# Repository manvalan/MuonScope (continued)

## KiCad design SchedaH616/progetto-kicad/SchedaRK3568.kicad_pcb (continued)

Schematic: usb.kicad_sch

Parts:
C801: 1uF; C_0603_1608Metric
C802: 100uF/10V; C_1210_3225Metric
C803: 0.1uF; C_0603_1608Metric
J801: TYPE-C-31-M-12; USB-C_SMD-TYPE-C-31-M-12_1; MPN TYPE-C-31-M-12
L801: 90R@100MHz; L_CommonModeChoke_Coilcraft_0805USB; not fitted
R801: 26.1k 1%; R_0603_1608Metric
R802: 100k; R_0603_1608Metric
R804, R805: 22k; R_0603_1608Metric
R806, R807: 2.2R; R_0402_1005Metric
U801: TPS2553DBVR; TPS2553DBVR_SOT-23-6_L2.9-W1.6-P0.95-LS2.8-BR; MPN TPS2553DBVR
U802: USBLC6-2SC6; SOT-23-6; MPN USBLC6-2SC6

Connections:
/5V_SYS: C801.1, R804.1, R805.1, U801.1 (IN); also elsewhere on the board
GND_D: C801.2, C802.2, C803.2, J801.1 (EH), J801.2 (EH), J801.3 (EH), J801.4 (EH), J801.A1B12 (GND), J801.B1A12 (GND), R801.2, R802.2, U801.2 (GND), U802.2 (GND); also elsewhere on the board
USB1_CC1: J801.A5 (CC1), R804.2
USB1_CC2: J801.B5 (CC2), R805.2
USB1_DM: L801.3, R807.1; also elsewhere on the board
USB1_DM_C: J801.A7 (DN1), J801.B7 (DN2), L801.4, R807.2, U802.3 (I/O2), U802.4 (I/O2)
USB1_DP: L801.1, R806.1; also elsewhere on the board
USB1_DP_C: J801.A6 (DP1), J801.B6 (DP2), L801.2, R806.2, U802.1 (I/O1), U802.6 (I/O1)
USB1_ILIM: R801.1, U801.5 (ILIM)
USB1_OC_N: U801.4 (/FAULT); also elsewhere on the board
USB1_VBUS: C802.1, C803.1, J801.A4B9 (VBUS), J801.B4A9 (VBUS), U801.6 (OUT), U802.5 (VBUS)
USB1_VBUS_EN: R802.1, U801.3 (EN); also elsewhere on the board

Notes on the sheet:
USB HOST: USB3_HOST1_DP/DM dell'RK3568 (parte USB 2.0, alimentata da USB3_AVDD) su USB-C (16 pin, HRO TYPE-C-31-M-12), solo host. Serie 8xx. Net USB1_* globali.
La porta non alimenta mai la scheda: VBUS esce solo dal load switch. Rp fissi da 22k a 5V_SYS su CC1/CC2 = sorgente 1.5 A (Type-C), niente controller PD.
TPS2553: EN attivo alto da GPIO0_A6 con 100k a GND, FAULT open-drain su GPIO0_B6 (pull-up 10k a VCC3V3_PMU sul foglio CPU).
RILIM 26.1k 1% = 0.91 / 0.99 / 1.08 A (min/nom/max, tabella 2 del datasheet).
J801 USB-C: DP/DM collegati su entrambi i lati (A6/B6, A7/B7), SBU non connessi, schermo a GND.
Rp 22k a 5 V = 1.5 A (tabella Type-C). Il TPS2553 limita comunque a circa 1 A.
ESD USBLC6-2SC6 vicino al connettore su DP/DM e VBUS. 2.2R in serie (Hardware Design Guide RK3568, USB3_HOST1_DP/DM) in parallelo al choke di modo comune DNP.

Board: 6 copper layers, 443 parts (75 on the bottom side), 314 nets, no tracks yet.

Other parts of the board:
H1, H2, H3, H4: MountingHole_2.2mm_M2

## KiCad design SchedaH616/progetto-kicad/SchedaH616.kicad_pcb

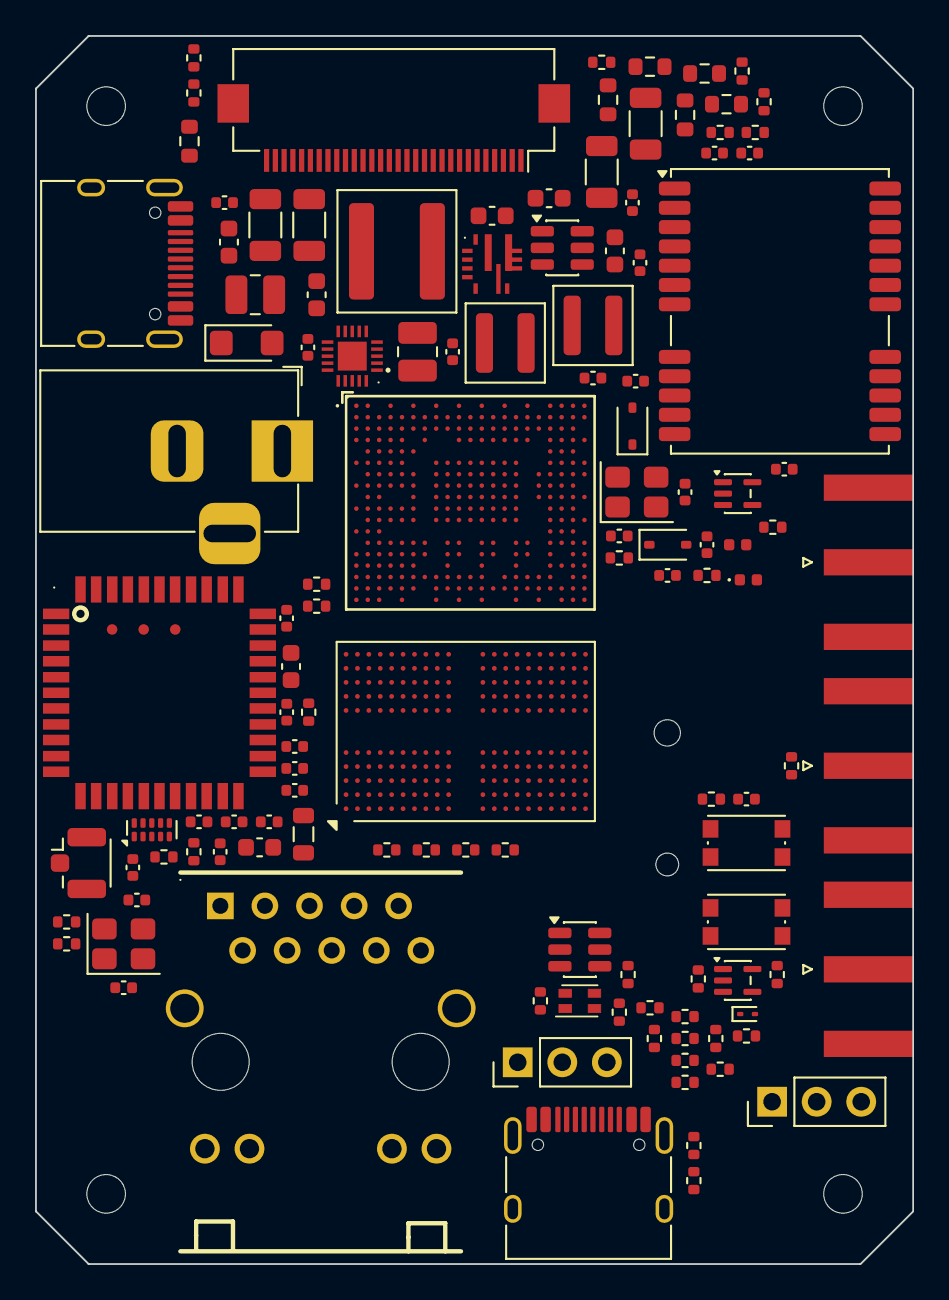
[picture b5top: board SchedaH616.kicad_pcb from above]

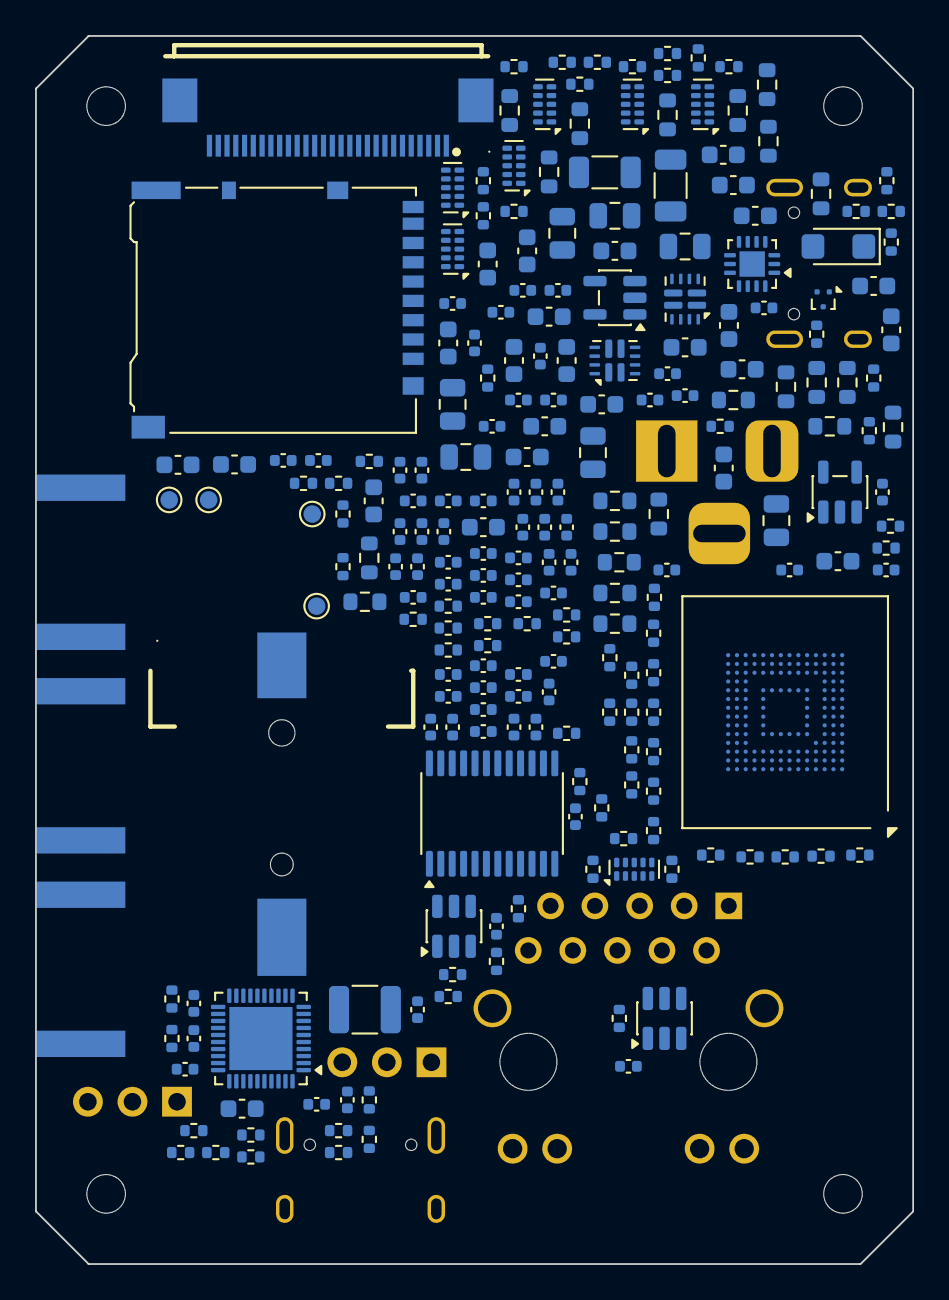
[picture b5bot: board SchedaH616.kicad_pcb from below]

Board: 6 copper layers, 50.0 x 70.0 mm, 356 parts (230 on the bottom side), 289 nets, no tracks yet.

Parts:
BT701: CR1220; BatteryHolder_MYOUNG_BS-12-B3AA003_CR1220
C101, C102: 10uF/25V; C_1206_3216Metric
C103, C109, C110, C132: 100nF; C_0603_1608Metric
C104, C105, C127, C128: 22uF/10V; C_1206_3216Metric
C106, C113, C220, C221: 22uF/10V; C_0805_2012Metric
C107: 4.7uF/10V; C_0603_1608Metric
C108: 1uF; C_0603_1608Metric
C111, C112, C114, C133, C134: 1uF/10V; C_0603_1608Metric
C115, C135: 10uF/10V; C_0805_2012Metric
C125: 100nF/50V; C_0603_1608Metric
C126: 100pF; C_0603_1608Metric
C201, C202, C203: 22uF/10V; C_0603_1608Metric
C204, C205, C206, C216, C218, C219, C226, C227, C228, C230, C501, C514: 100nF; C_0402_1005Metric
C207, C222, C223, C401, C402, C403, C404, C411, C412, C415: 1uF/10V; C_0402_1005Metric
C208, C209, C210, C211, C212, C215, C229: 47uF/6.3V; C_0603_1608Metric
C213, C224, C225, C308, C309, C313, C314, C315, C317, C324, C331, C604, C703, C801: 1uF; C_0402_1005Metric
C214, C231: 4.7uF/10V; C_0402_1005Metric
C217: 10uF/16V; C_0805_2012Metric
C301, C302: 12pF/50V; C_0402_1005Metric
C303: 220nF/16V; C_0402_1005Metric
C304: 1nF/50V; C_0402_1005Metric
C305, C310, C335: 10uF/6.3V; C_0603_1608Metric
C306, C307, C311, C312, C334: 2.2uF/6.3V; C_0402_1005Metric
C316, C318, C319, C320, C321, C322, C323, C325, C326, C327, C328, C332, C333, C405, C406, C407, C408, C409, C410, C413, C414, C417, C418, C420, C421, C423, C505, C506, C507, C508, C510, C511, C512, C513, C515, C602, C605, C702, C705, C706, C803: 0.1uF; C_0402_1005Metric
C329, C330: 470nF/16V; C_0402_1005Metric
C416, C419: 2.2uF/10V; C_0402_1005Metric
C422: 10uF/10V; C_0603_1608Metric
C502, C503: 15pF; C_0402_1005Metric
C504: 22uF; C_0603_1608Metric
C509, C601, C701: 10uF; C_0603_1608Metric
C603: 4.7uF; C_0603_1608Metric
C606, C607: DNP; C_0402_1005Metric
C704: 10nF; C_0402_1005Metric
C802: 100uF/10V; C_1210_3225Metric
D101, D102: SMF5.0A; D_SMF
D701, D704: BAT54; D_SOD-323
D702: ESD5V3U1U-02LS; D_0402_1005Metric
D703: ESD9B5.0ST5G; D_SOD-923
H1, H2, H3, H4: MountingHole_2.2mm_M2
J1: BUS_POWER_MIKILAB; Hirose_FH12-30S-0.5SH_1x30-1MP_P0.50mm_Horizontal
J2: BUS_MIKILAB_MAIN; FPC-05F-28PH20
J103: DC-005-5A-2.0; BarrelJack_Horizontal
J104, J801: TYPE-C-31-M-12; USB_C_Receptacle_HRO_TYPE-C-31-M-12
J301: UART0 debug; PinHeader_1x03_P2.54mm_Vertical
J401: DM3AT-SF-PEJM5; microSD_HC_Hirose_DM3AT-SF-PEJM5
J501: HR911130C; RJ45-TH_HR911130C
J601: U.FL; U.FL_Hirose_U.FL-R-SMT-1_Vertical
J701: SMA antenna; SMA_Amphenol_132289_EdgeMount
J702: SMA PPS OUT; SMA_Amphenol_132289_EdgeMount
J703: SMA STROBE IN; SMA_Amphenol_132289_EdgeMount
J704: PPS/STROBE; PinHeader_1x03_P2.54mm_Vertical
L101: 3.3uH/8A; L_Coilcraft_XAL6030-XXX
L201: 1uH/2.5A; L_1008_2520Metric
L202: 1uH/4A; L_Coilcraft_XAL4020-XXX
L203: 1uH/3A; L_1008_2520Metric
L204: 2.2uH/4A; L_Coilcraft_XAL4020-XXX
L501: 2.2uH; L_0805_2012Metric
L701: 27nH; L_0402_1005Metric
L801: 90R@100MHz; L_CommonModeChoke_Coilcraft_0805USB
R1, R2, R3, R4: 0R; R_0603_1608Metric
R101: 169k 1%; R_0603_1608Metric
R102: 36.1k 1%; R_0603_1608Metric
R103: 73.2k 1%; R_0603_1608Metric
R104, R106, R108, R110, R122, R124, R126: 10k 1%; R_0603_1608Metric
R105, R121: 32.4k 1%; R_0603_1608Metric
R107, R109, R123, R125: 46.4k 1%; R_0603_1608Metric
R111, R127: 22.1k 1%; R_0603_1608Metric
R112: 6.8k 1%; R_0603_1608Metric
R113, R115, R128: 100k; R_0603_1608Metric
R114: 10k; R_0603_1608Metric
R116: 20k; R_0603_1608Metric
R201, R302, R317, R318, R319, R320, R321, R323, R330, R331, R332, R333, R334, R339, R340, R341, R342, R343, R344, R345, R346, R347, R407, R408, R409, R410, R411, R412, R413, R414, R415, R416, R423, R518, R521, R603, R604, R605, R606, R607: 10k; R_0402_1005Metric
R202, R301, R303, R336, R405, R520, R608, R806, R807: 0R; R_0402_1005Metric
R203, R322, R601, R602, R706, R802: 100k; R_0402_1005Metric
R204: 33.2k 1%; R_0402_1005Metric
R205: 10k 1%; R_0402_1005Metric
R304, R403, R404: 240R 1%; R_0402_1005Metric
R305, R306, R307, R308, R309, R310, R406, R417, R703, R704: 33R; R_0402_1005Metric
R311, R312, R313, R314, R315, R316, R338, R705: 100R; R_0402_1005Metric
R324, R325, R507, R508, R509, R510, R511, R512, R513, R514, R515, R517: 4.7k; R_0402_1005Metric
R326, R327, R328, R329: 2.2k; R_0402_1005Metric
R337: 150k 1%; R_0402_1005Metric
R401, R402: 100k 1%; R_0402_1005Metric
R418, R419, R420, R421, R422: 47k; R_0402_1005Metric
R501, R502, R503, R504, R505, R506: 22R; R_0402_1005Metric
R516: 1.5k; R_0402_1005Metric
R519: 2.49k 1%; R_0402_1005Metric
R522, R523: 510R; R_0402_1005Metric
R702: 10R; R_0402_1005Metric
R801: 26.1k 1%; R_0402_1005Metric
R804, R805: 22k; R_0402_1005Metric
SW301: RESET; SW_Push_1P1T_NO_CK_KMR2
SW302: FEL; SW_Push_1P1T_NO_CK_KMR2
TP101: MUX2_ST; TestPoint_Pad_D1.0mm
TP201: PWRON; TestPoint_Pad_D1.0mm
TP701: SAFEBOOT_N; TestPoint_Pad_D1.0mm
TP702: RESET_N; TestPoint_Pad_D1.0mm
U101: TPS56637RPAR; Texas_RPA0010A_VQFN-HR-10_3x3mm
U103, U108: TPS2121RUXR; Texas_VQFN-HR-12_2x2.5mm_P0.5mm
U104: FUSB302BMPX; WQFN-14-1EP_2.5x2.5mm_P0.5mm_EP1.45x1.45mm
U105: SY6280AAC; SOT-23-5
U107: TPD2EUSB30ADRTR; Texas_DRT-3
U201: AXP313A; QFN-20_L3.0-W3.0-P0.40-BL-EP1.7
U202: TPS563201DDCR; SOT-23-6
U203: AP2112K-1.8TRG1; SOT-23-5
U301: H616; BGA-284_L14.0-W12.0-P0.65-TL
U302, U303, U304, U305, U306, U307, U403, U404: TPD4E05U06DQA; USON-10_2.5x1.0mm_P0.5mm
U308: TCA6416APWR; TSSOP-24_4.4x7.8mm_P0.65mm
U401: MT53E512M32D1ZW-046 IT:B; BGA-200_10x14.5mm_Layout12x22_P0.8x0.65mm
U402: FEMDNN064G-C9A61; LFBGA-153_11.5x13mm_Layout14x14_P0.5mm
U501: RTL8211F-CG; QFN-40-1EP_5x5mm_P0.4mm_EP3.6x3.6mm
U502: 25AA02E48T-I/OT; SOT-23-6
U601: AP6256; AP6256_LGA-47_12x12mm
U701: NEO-M9N-00B; ublox_NEO
U702, U703: 74LVC1G17; SOT-353_SC-70-5
U801: TPS2553DBVR; SOT-23-6
U802: USBLC6-2SC6; SOT-23-6
Y301: 24MHz; Crystal_SMD_3225-4Pin_3.2x2.5mm
Y501: 25MHz; Crystal_SMD_3225-4Pin_3.2x2.5mm

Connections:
/3V3_PERI: C220.1, C221.1, C222.1, C416.1, C417.1, C418.1, C422.1, C423.1, C509.1, C510.1, C511.1, C512.1, C513.1, C515.1, C601.1, C602.1, C701.1, C702.1, C705.1, C706.1, D701.2, J401.4, L204.2, R204.1, R418.1, R419.1, R420.1, R421.1, R422.1, R507.1, R511.1, R512.1, R513.1, R516.1, R517.1, R518.1, R521.1, U203.1, U203.3, U402.E6, U402.F5, U402.J10, U402.K9, U501.11, U501.28, U501.29, U501.40, U502.6, U601.9, U601.23, U701.23, U702.5, U703.5
/3V3_SYS: C108.1, C109.1, R336.2, U104.3, U104.4
/5V_SYS: C113.1, C114.1, C201.1, C202.1, C203.1, C204.1, C205.1, C206.1, C217.1, C218.1, C801.1, R203.1, R804.1, R805.1, U103.1, U103.8, U201.2, U201.17, U201.20, U202.3, U801.1
/AP-RESET: R201.2, R338.1, U201.13
/Alimentazione/5V_BUCK: C104.1, C105.1, C127.1, C128.1, C133.1, L101.2, R103.1, R115.1, R116.1, R121.1, R123.1, U108.7
/Alimentazione/5V_EXT: C111.1, C115.1, C135.1, R105.1, R107.1, R128.1, U103.7, U105.5, U108.1, U108.8
/Alimentazione/5V_JACK: C106.1, C134.1, D101.1, J103.1, R125.1, U108.2
/Alimentazione/BUCK_BST: C103.1, U101.7
/Alimentazione/BUCK_EN: R101.2, R102.1, U101.1
/Alimentazione/BUCK_FB: C126.2, R103.2, R104.1, U101.2
/Alimentazione/BUCK_FF: C126.1, R116.2
/Alimentazione/BUCK_MODE: R114.1, U101.10
/Alimentazione/BUCK_PG: R115.2, U101.4
/Alimentazione/BUCK_SW: C103.2, L101.1, U101.6
/Alimentazione/MUX2_ILM: R127.1, U108.10
/Alimentazione/MUX2_OV1: R123.2, R124.1, U108.5
/Alimentazione/MUX2_OV2: R125.2, R126.1, U108.4
/Alimentazione/MUX2_PR1: R121.2, R122.1, U108.6
/Alimentazione/MUX2_SS: C132.1, U108.11
/Alimentazione/MUX2_ST: R128.2, TP101.1, U108.9
/Alimentazione/MUX_ILM: R111.1, U103.10
/Alimentazione/MUX_OV1: R107.2, R108.1, U103.5
/Alimentazione/MUX_OV2: R109.2, R110.1, U103.4
/Alimentazione/MUX_PR1: R105.2, R106.1, U103.6
/Alimentazione/MUX_SS: C110.1, U103.11
/Alimentazione/SRC_ISET: R112.1, U105.3
/Alimentazione/USBC_CC1: J104.A5, U104.10, U104.11, U107.1
/Alimentazione/USBC_CC2: J104.B5, U104.1, U104.14, U107.2
/Alimentazione/VBUS: C107.1, C112.1, D102.1, J104.A4, J104.A9, J104.B4, J104.B9, R109.1, U103.2, U104.2, U105.1
/Bus MIKILAB/BUS_1V25_REF: J1.6, J2.6
/Bus MIKILAB/BUS_2V5_REF: J1.5, J2.5
/Bus MIKILAB/BUS_3V3: J1.9, J1.29, J2.3
/Bus MIKILAB/BUS_5V: J1.8, J2.2
/Bus MIKILAB/BUS_VBIAS_1: J1.2, J2.8
/Bus MIKILAB/BUS_VBIAS_2: J1.3, J2.9
/Bus MIKILAB/SPI_ID_0: J2.25, R1.1
/Bus MIKILAB/SPI_ID_1: J2.26, R2.1
/Bus MIKILAB/SPI_ID_2: J2.27, R3.1
/CPU/DCXO_XIN: C301.1, U301.B11, Y301.1
/CPU/DCXO_XOUT: R301.1, U301.C12
/CPU/DCXO_XOUT_R: C302.1, R301.2, Y301.3
/CPU/IOX_INT_N: R330.2, U301.C1, U308.1
/CPU/IOX_RESET_N: R331.2, U308.3
/CPU/SOC_AC_VRA1: C331.1, U301.C17
/CPU/SOC_ADDR_0: R311.1, U301.C3
/CPU/SOC_ADDR_1: R312.1, U301.A2
/CPU/SOC_ADDR_2: R313.1, U301.B2
/CPU/SOC_AGND: C329.2, C330.2, R303.1, R337.2, U301.H18
/CPU/SOC_BOOT_SEL1: R340.2, R341.1, U301.D1
/CPU/SOC_BOOT_SEL2: R342.2, R343.1, U301.D2
/CPU/SOC_DXLDO: C303.1, U301.D13
/CPU/SOC_FEL: R302.2, SW302.1, U301.B17
/CPU/SOC_PREFIX_0: R314.1, U301.H5
/CPU/SOC_PREFIX_1: R315.1, U301.K6
/CPU/SOC_PREFIX_2: R316.1, U301.K2
/CPU/SOC_RESET: C304.1, R338.2, R339.2, SW301.1, U301.A16
/CPU/SOC_REXT: R337.1, U301.K18
/CPU/SOC_SZQ: R304.1, U301.L15
/CPU/SOC_VRA1: C329.1, U301.J18
/CPU/SOC_VRA2: C330.1, U301.J17
/CPU/UART0_RX: J301.2, U301.D15
/CPU/UART0_TX: J301.1, U301.D16
/DAC61402_FAULT: J1.20, R323.2, U304.1, U308.6
/MAIN_HIT_N: J2.28, R325.2, U301.C9, U307.4
/MAIN_I2C_SCL: J2.15, R326.2, U301.B15, U305.2
/MAIN_I2C_SDA: J2.14, R327.2, U301.C15, U305.1
/MAIN_SPI_ADDR_0: J2.18, R311.2, U305.5
/MAIN_SPI_ADDR_1: J2.19, R312.2, U306.1
/MAIN_SPI_ADDR_2: J2.20, R313.2, U306.2
/MAIN_SPI_ALERT_N: J2.24, R324.2, U301.B10, U307.2
/MAIN_SPI_CS_MASTER: J2.17, R320.2, U301.B14, U305.4
/MAIN_SPI_MISO: J2.13, R310.2, U304.5
/MAIN_SPI_MOSI: J2.12, R309.2, U304.4
/MAIN_SPI_PREFIX_0: J2.21, R314.2, U306.4
/MAIN_SPI_PREFIX_1: J2.22, R315.2, U306.5
/MAIN_SPI_PREFIX_2: J2.23, R316.2, U307.1
/MAIN_SPI_SCLK: J2.11, R308.2, U304.2
/Memorie/LP_ODT_A: R401.2, U401.G2
/Memorie/LP_ODT_B: R402.2, U401.T2
/Memorie/LP_ZQ0: R403.2, U401.A5
/Memorie/LP_ZQ1: R404.2, U401.A8
/PD_INT_N: R332.2, U104.5, U301.F4
/PMIC/PERI_BST: C219.1, U202.6
/PMIC/PERI_EN: R202.2, R203.2, U202.5
/PMIC/PERI_FB: R204.2, R205.1, U202.4
/PMIC/PERI_SW: C219.2, L204.1, U202.2
/PMIC/PMU_LX1: L201.1, U201.18
/PMIC/PMU_LX2: L202.1, U201.19
/PMIC/PMU_LX3: L203.1, U201.3
/PMIC/PMU_PWRON: C216.1, TP201.1, U201.14
/PMIC/PMU_RTCLDO: C231.1, U201.7
/PMIC/PMU_VREF: C207.1, U201.8
/PMU-SCK: R328.2, U104.6, U201.6, U301.C18, U308.22
/PMU-SDA: R329.2, U104.7, U201.5, U301.B18, U308.23
/PWR_SPI_DAC_CS: J1.17, R319.2, U301.B13, U303.2
/PWR_SPI_INA239A_CS: J1.15, R317.2, U301.A12, U302.5
/PWR_SPI_INA239B_CS: J1.16, R318.2, U301.A14, U303.1
/PWR_SPI_MISO: J1.13, R307.2, U302.4
/PWR_SPI_MOSI: J1.12, R306.2, U302.2
/PWR_SPI_SCLK: J1.11, R305.2, U302.1
/PWR_SRC_ST: R334.2, U103.9, U308.9
/Rete/ETH_CT: C514.1, J501.P1
/Rete/ETH_LED1_A: J501.11, R522.2
/Rete/ETH_LED2_A: J501.14, R523.2
/Rete/MDI0_N: J501.P3, U501.2
/Rete/MDI0_P: J501.P2, U501.1
/Rete/MDI1_N: J501.P7, U501.5
/Rete/MDI1_P: J501.P4, U501.4
/Rete/MDI2_N: J501.P6, U501.7
/Rete/MDI2_P: J501.P5, U501.6
/Rete/MDI3_N: J501.P9, U501.10
/Rete/MDI3_P: J501.P8, U501.9
/USB0_DM: J104.A7, J104.B7, U301.J19
/USB0_DP: J104.A6, J104.B6, U301.J20
/VBIAS_ENABLE: J1.19, R322.1, U303.5, U308.5
/VBUS_SRC_EN: R113.1, U105.4, U308.8
/VCC-1V8: C214.1, C317.1, C318.1, C319.1, C320.1, C321.1, C322.1, C332.1, C334.1, C335.1, C411.1, C412.1, C413.1, C414.1, R201.1, R328.1, R329.1, R331.1, R339.1, U201.15, U301.D11, U301.D12, U301.D18, U301.F18, U301.H17, U301.H20, U301.L14, U308.2, U401.F1, U401.F12, U401.G4, U401.G9, U401.T4, U401.T9, U401.U1, U401.U12
/VCC-1V8-EMMC: C223.1, C323.1, C419.1, C420.1, C421.1, R330.1, R332.1, R333.1, R340.1, R342.1, R344.1, R346.1, R407.1, R408.1, R409.1, R410.1, R411.1, R412.1, R413.1, R414.1, R415.1, R416.1, U203.5, U301.F5, U402.C6, U402.M4, U402.N4, U402.P3, U402.P5
/VCC-DRAM: C212.1, C213.1, C229.1, C230.1, C314.1, C315.1, C316.1, C401.1, C402.1, C403.1, C404.1, C405.1, C406.1, C407.1, C408.1, C409.1, C410.1, L203.2, R401.1, R402.1, R403.1, R404.1, R405.1, U301.L9, U301.L10, U301.L11, U301.L12, U301.L13, U401.A4, U401.A9, U401.AA3, U401.AA5, U401.AA8, U401.AA10, U401.AB4, U401.AB9, U401.B3, U401.B5, U401.B8, U401.B10, U401.D1, U401.D5, U401.D8, U401.D12, U401.F3, U401.F5, U401.F8, U401.F10, U401.H1, U401.H5, U401.H8, U401.H12, U401.K1, U401.K3, U401.K10, U401.K12, U401.N1, U401.N3, U401.N10, U401.N12, U401.R1, U401.R5, U401.R8, U401.R12, U401.U3, U401.U5, U401.U8, U401.U10, U401.W1, U401.W5, U401.W8, U401.W12
/VCC-DRAM-FB: R405.2, U201.4
/VCC-IO: C215.1, C226.1, C324.1, C325.1, C326.1, C327.1, C328.1, C333.1, C604.1, C605.1, R202.1, R302.1, R317.1, R318.1, R319.1, R320.1, R323.1, R324.1, R325.1, R326.1, R327.1, R334.1, R336.1, R423.1, R603.1, R604.1, R605.1, R606.1, R607.1, U201.12, U301.D7, U301.D10, U301.E18, U301.J6, U301.M18, U308.24, U601.22
/VDD-CPU: C210.1, C211.1, C225.1, C228.1, C305.1, C306.1, C307.1, C308.1, C309.1, L202.2, U301.H8, U301.H9, U301.J8, U301.J9, U301.J10, U301.J11
/VDD-CPUFB: U201.1, U301.L8
/VDD-SYS: C208.1, C209.1, C224.1, C227.1, C310.1, C311.1, C312.1, C313.1, L201.2, U301.F9, U301.F10, U301.F11, U301.F12, U301.F13, U301.G8, U301.G9, U301.G10, U301.G11, U301.G12
/VDD-SYSFB: U201.16, U301.F8
/VIN_SYS: C101.1, C102.1, C125.1, J1.24, J1.25, J1.26, R101.1, U101.8
/VREF_ENABLE: J1.18, R321.1, U303.4, U308.4
BT_HOST_WAKE: U308.16, U601.7
BT_REG_ON: R602.1, U308.14, U601.34
BT_UART_CTS: U301.B3, U601.41
BT_UART_RTS: U301.C4, U601.44
BT_UART_RX: U301.B4, U601.42
BT_UART_TX: U301.A4, U601.43
BT_WAKE: U308.15, U601.6
DRAM_A0: U301.T21, U401.H9, U401.R9
DRAM_A1: U301.U17, U401.H2, U401.R2
DRAM_A2: U301.T18, U401.H4, U401.R4
DRAM_A3: U301.T16, U401.J11, U401.P11
DRAM_A4: U301.R18, U401.H11, U401.R11
DRAM_A5: U301.P15, U401.H3, U401.R3
DRAM_CKE0: U301.V15, U401.J4, U401.P4
DRAM_CKE1: U301.P13, U401.J5, U401.P5
DRAM_CKN: U301.U14, U401.J9, U401.P9
DRAM_CKP: U301.T14, U401.J8, U401.P8
DRAM_CS0: U301.V17, U401.J2, U401.P2
DRAM_CS1: U301.R20, U401.H10, U401.R10
DRAM_DQ0: U301.N3, U401.B2
DRAM_DQ1: U301.U4, U401.C2
DRAM_DQ2: U301.N2, U401.E2
DRAM_DQ3: U301.T4, U401.F2
DRAM_DQ4: U301.U3, U401.F4
DRAM_DQ5: U301.P1, U401.E4
DRAM_DQ6: U301.T2, U401.C4
DRAM_DQ7: U301.P2, U401.B4
DRAM_DQ8: U301.P5, U401.B11
DRAM_DQ9: U301.V3, U401.C11
DRAM_DQ10: U301.P4, U401.E11
DRAM_DQ11: U301.R4, U401.F11
DRAM_DQ12: U301.R6, U401.F9
DRAM_DQ13: U301.N4, U401.E9
DRAM_DQ14: U301.P6, U401.C9
DRAM_DQ15: U301.N5, U401.B9
DRAM_DQ16: U301.T11, U401.AA2
DRAM_DQ17: U301.U12, U401.Y2
DRAM_DQ18: U301.T12, U401.V2
DRAM_DQ19: U301.U9, U401.U2
DRAM_DQ20: U301.T6, U401.U4
DRAM_DQ21: U301.U5, U401.V4
DRAM_DQ22: U301.T7, U401.Y4
DRAM_DQ23: U301.T5, U401.AA4
DRAM_DQ24: U301.R9, U401.AA11
DRAM_DQ25: U301.P7, U401.Y11
DRAM_DQ26: U301.N7, U401.V11
DRAM_DQ27: U301.P9, U401.U11
DRAM_DQ28: U301.P10, U401.U9
DRAM_DQ29: U301.U11, U401.V9
DRAM_DQ30: U301.P12, U401.Y9
DRAM_DQ31: U301.R12, U401.AA9
DRAM_DQM0: U301.U1, U401.C3
DRAM_DQM1: U301.R3, U401.C10
DRAM_DQM2: U301.T9, U401.Y3
DRAM_DQM3: U301.N10, U401.Y10
DRAM_DQS0N: U301.R1, U401.E3
DRAM_DQS0P: U301.R2, U401.D3
DRAM_DQS1N: U301.V2, U401.E10
DRAM_DQS1P: U301.U2, U401.D10
DRAM_DQS2N: U301.U8, U401.V3
DRAM_DQS2P: U301.V8, U401.W3
DRAM_DQS3N: U301.U10, U401.V10
DRAM_DQS3P: U301.V10, U401.W10
DRAM_RST: U301.U21, U401.T11
EMMC_CLK: R344.2, R345.1, R406.1, U301.D3
EMMC_CLK_M: R406.2, U402.M6
EMMC_CMD: R346.2, R347.1, R407.2, U301.E2, U402.M5
EMMC_D0: R408.2, U301.F2, U402.A3
EMMC_D1: R409.2, U301.G3, U402.A4
EMMC_D2: R410.2, U301.H2, U402.A5
EMMC_D3: R411.2, U301.E3, U402.B2
EMMC_D4: R412.2, U301.F1, U402.B3
EMMC_D5: R413.2, U301.F3, U402.B4
EMMC_D6: R414.2, U301.H1, U402.B5
EMMC_D7: R415.2, U301.H3, U402.B6
EMMC_DS: U301.B1, U402.H5
EMMC_RST: R416.2, U301.C2, U402.K5
EMMC_VDDI: C415.1, U402.C2
GND_A: J1.1, J1.4, J1.7, J2.7, R4.1
GND_D: BT701.2, C101.2, C102.2, C104.2, C105.2, C106.2, C107.2, C108.2, C109.2, C110.2, C111.2, C112.2, C113.2, C114.2, C115.2, C125.2, C127.2, C128.2, C132.2, C133.2, C134.2, C135.2, C201.2, C202.2, C203.2, C204.2, C205.2, C206.2, C207.2, C208.2, C209.2, C210.2, C211.2, C212.2, C213.2, C214.2, C215.2, C216.2, C217.2, C218.2, C220.2, C221.2, C222.2, C223.2, C224.2, C225.2, C226.2, C227.2, C228.2, C229.2, C230.2, C231.2, C301.2, C302.2, C303.2, C304.2, C305.2, C306.2, C307.2, C308.2, C309.2, C310.2, C311.2, C312.2, C313.2, C314.2, C315.2, C316.2, C317.2, C318.2, C319.2, C320.2, C321.2, C322.2, C323.2, C324.2, C325.2, C326.2, C327.2, C328.2, C331.2, C332.2, C333.2, C334.2, C335.2, C401.2, C402.2, C403.2, C404.2, C405.2, C406.2, C407.2, C408.2, C409.2, C410.2, C411.2, C412.2, C413.2, C414.2, C415.2, C416.2, C417.2, C418.2, C419.2, C420.2, C421.2, C422.2, C423.2, C501.2, C502.2, C503.2, C504.2, C505.2, C506.2, C507.2, C508.2, C509.2, C510.2, C511.2, C512.2, C513.2, C514.2, C515.2, C601.2, C602.2, C603.2, C604.2, C605.2, C606.2, C607.2, C701.2, C702.2, C703.2, C704.2, C705.2, C706.2, C801.2, C802.2, C803.2, D101.2, D102.2, D702.2, D703.2, J1.10, J1.14, J1.21, J1.22, J1.23, J1.27, J1.28, J1.30, J1.MP, J2.1, J2.4, J2.10, J2.16, J2.MP, J103.2, J103.3, J104.A1, J104.A12, J104.B1, J104.B12, J104.SH, J301.3, J401.6, J401.10, J401.SH, J501.12, J501.13, J501.P10, J501.SHIELD0, J501.SHIELD1, J601.2, J701.2, J702.2, J703.2, J704.3, J801.A1, J801.A12, J801.B1, J801.B12, J801.SH, R1.2, R2.2, R3.2, R4.2, R102.2, R104.2, R106.2, R108.2, R110.2, R111.2, R112.2, R113.2, R114.2, R122.2, R124.2, R126.2, R127.2, R205.2, R303.2, R304.2, R321.2, R322.2, R341.2, R343.2, R345.2, R347.2, R508.2, R509.2, R510.2, R514.2, R515.2, R519.2, R601.2, R602.2, R706.2, R801.2, R802.2, SW301.2, SW302.2, U101.3, U101.9, U103.3, U103.12, U104.8, U104.9, U104.15, U105.2, U107.3, U108.3, U108.12, U201.9, U201.21, U202.1, U203.2, U301.A1, U301.A10, U301.A18, U301.A21, U301.B6, U301.B16, U301.D19, U301.F14, U301.F15, U301.G13, U301.G14, U301.G15, U301.H10, U301.H11, U301.H12, U301.H13, U301.H14, U301.H15, U301.H19, U301.J12, U301.J13, U301.J14, U301.J15, U301.K8, U301.K9, U301.K10, U301.K11, U301.K12, U301.K13, U301.K14, U301.K15, U301.L21, U301.M1, U301.M2, U301.M3, U301.N6, U301.N9, U301.N12, U301.N15, U301.N18, U301.P3, U301.R5, U301.R21, U301.T1, U301.T3, U301.T8, U301.T10, U301.T15, U301.T17, U301.U6, U301.U13, U301.V1, U301.V5, U301.V12, U301.V19, U301.V21, U302.3, U302.8, U303.3, U303.8, U304.3, U304.8, U305.3, U305.8, U306.3, U306.8, U307.3, U307.8, U308.12, U308.21, U401.A3, U401.A10, U401.AB3, U401.AB5, U401.AB8, U401.AB10, U401.C1, U401.C5, U401.C8, U401.C12, U401.D2, U401.D4, U401.D9, U401.D11, U401.E1, U401.E5, U401.E8, U401.E12, U401.G1, U401.G3, U401.G5, U401.G8, U401.G10, U401.G12, U401.J1, U401.J3, U401.J10, U401.J12, U401.K2, U401.K4, U401.K9, U401.K11, U401.N2, U401.N4, U401.N9, U401.N11, U401.P1, U401.P3, U401.P10, U401.P12, U401.T1, U401.T3, U401.T5, U401.T8, U401.T10, U401.T12, U401.V1, U401.V5, U401.V8, U401.V12, U401.W2, U401.W4, U401.W9, U401.W11, U401.Y1, U401.Y5, U401.Y8, U401.Y12, U402.A6, U402.C4, U402.E7, U402.G5, U402.H10, U402.J5, U402.K8, U402.N2, U402.N5, U402.P4, U402.P6, U403.3, U403.8, U404.3, U404.8, U501.41, U502.2, U601.1, U601.3, U601.20, U601.29, U601.31, U601.33, U601.36, U701.7, U701.10, U701.12, U701.13, U701.24, U702.3, U703.3, U801.2, U802.2, Y301.2, Y301.4, Y501.2, Y501.4
GNSS_ANT_BIAS: C704.1, L701.1, R702.2
GNSS_BAT: BT701.1, D704.2
GNSS_EXTINT: U301.B9, U701.4, U703.4
GNSS_PPS: R703.2, U301.C10
GNSS_PPS_BUF: R704.1, U702.4
GNSS_PPS_OUT: J702.1, J704.1, R704.2
GNSS_RESET_N: TP702.1, U701.8
GNSS_RF_IN: D702.1, J701.1, L701.2, U701.11
GNSS_SAFEBOOT_N: TP701.1, U701.1
GNSS_STROBE_IN: D703.1, J703.1, J704.2, R705.1
GNSS_STROBE_R: R705.2, R706.1, U703.2
GNSS_TP: R703.1, U701.3, U702.2
GNSS_UART2_RX: U301.B8, U701.20
GNSS_UART2_TX: U301.A8, U701.21
GNSS_VCC_RF: R702.1, U701.9
GNSS_V_BCKP: C703.1, D701.1, D704.1, U701.22
PHY_CLKOUT: R520.1, U501.35
PHY_EE_CS_N: R521.2, U308.19, U502.5
PHY_INT_N: R517.2, U308.11, U501.31
PHY_LED0: R513.2, U501.32
PHY_LED1: R514.1, R522.1, U501.33
PHY_LED2: R515.1, R523.1, U501.34
PHY_MDC: U301.L6, U501.13
PHY_MDIO: R516.2, U301.L4, U501.14
PHY_REG_OUT: L501.1, U501.30
PHY_RSET: R519.1, U501.39
PHY_RST_N: C501.1, R518.2, U308.10, U501.12
PHY_TXCTL_P: R506.2, U501.19
PHY_TXC_P: R501.2, U501.20
PHY_TXD0_P: R502.2, U501.18
PHY_TXD1_P: R503.2, U501.17
PHY_TXD2_P: R504.2, U501.16
PHY_TXD3_P: R505.2, U501.15
PHY_VDD10: C504.1, C505.1, C506.1, C507.1, C508.1, L501.2, U501.3, U501.8, U501.21, U501.38
PHY_XI: C502.1, U501.36, Y501.1
PHY_XO: C503.1, U501.37, Y501.3
RGMII_CLKIN: R520.2, U301.E5
RGMII_RXCK: R508.1, U301.G5, U501.27
RGMII_RXCTL: R509.1, U301.H4, U501.26
RGMII_RXD0: R512.2, U301.E4, U501.25
RGMII_RXD1: R511.2, U301.G6, U501.24
RGMII_RXD2: R510.1, U301.D4, U501.23
RGMII_RXD3: R507.2, U301.H6, U501.22
RGMII_TXCK: R501.1, U301.K4
RGMII_TXCTL: R506.1, U301.K5
RGMII_TXD0: R502.1, U301.L5
RGMII_TXD1: R503.1, U301.D5
RGMII_TXD2: R504.1, U301.E6
RGMII_TXD3: R505.1, U301.G4
SD_CLK: R417.1, U301.K1
SD_CLK_S: J401.5, R417.2, U403.1
SD_CMD: J401.3, R418.2, U301.K3, U403.2
SD_D0: J401.7, R419.2, U301.J3, U403.4
SD_D1: J401.8, R420.2, U301.J2, U403.5
SD_D2: J401.1, R421.2, U301.L3, U404.1
SD_D3: J401.2, R422.2, U301.L2, U404.2
SD_DET: J401.9, R423.2, U308.18, U404.4
SPI1_CLK: R305.1, R308.1, U301.C14, U502.1
SPI1_MISO: R307.1, R310.1, U301.C13, U502.4
SPI1_MOSI: R306.1, R309.1, U301.B12, U502.3
USB1_CC1: J801.A5, R804.2
USB1_CC2: J801.B5, R805.2
USB1_DM: L801.3, R807.1, U301.M19
USB1_DM_C: J801.A7, J801.B7, L801.4, R807.2, U802.3, U802.4
USB1_DP: L801.1, R806.1, U301.M20
USB1_DP_C: J801.A6, J801.B6, L801.2, R806.2, U802.1, U802.6
USB1_ILIM: R801.1, U801.5
USB1_OC_N: R333.2, U301.G2, U801.4
USB1_VBUS: C802.1, C803.1, J801.A4, J801.A9, J801.B4, J801.B9, U801.6, U802.5
USB1_VBUS_EN: R802.1, U308.7, U801.3
WIFI_32K: U301.C8, U601.24
WL_ANT: C606.1, R608.1, U601.2
WL_ANT_C: C607.1, J601.1, R608.2
WL_HOST_WAKE: U308.17, U601.13
WL_LDO_OUT: C603.1, U601.21
WL_REG_ON: R601.1, U308.13, U601.12
WL_SDIO_CLK: U301.A6, U601.17
WL_SDIO_CMD: R603.2, U301.C7, U601.16
WL_SDIO_D0: R604.2, U301.C6, U601.18
WL_SDIO_D1: R605.2, U301.B5, U601.19
WL_SDIO_D2: R606.2, U301.C5, U601.14
WL_SDIO_D3: R607.2, U301.B7, U601.15

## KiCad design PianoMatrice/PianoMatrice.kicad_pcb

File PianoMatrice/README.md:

# PianoMatrice

Piano di rivelazione MuonScope con **16 fotodiodi VBPW34S in matrice 4×4 a passo 10 mm**, per il bus **MIKILAB REV5.1**. È la scheda definitiva del piano: i valori del front-end trovati sperimentalmente con il `PianoTest` si inseriscono come variabili di progetto.

Progetto KiCad 10: `PianoMatrice.kicad_pro`. Schema esportato in `PianoMatrice-schema.pdf`. Generatori Python in `generatori/`.

## Variabili da determinare sperimentalmente

Si impostano in *File → Impostazioni progetto → Variabili di testo* e si aggiornano schema, distinta materiali e serigrafia di tutti i 16 canali.

| Variabile | Default | Dove |
|---|---|---|
| `${RF}` | 100M | Resistenza di retroazione del preamplificatore di carica (R×11, R×31) |
| `${CF}` | 1p | Condensatore di retroazione (C×11, C×31) |
| `${VBIAS}` | 30V | Tensione di polarizzazione nominale (programmata nel DAC61402) |

Ogni canale ha anche una piazzola DNP in parallelo a Rf (Rf2) e una in parallelo a Cf (Cf2), per le prove.

## Fogli

| Foglio | Contenuto |
|---|---|
| Canali (8 istanze, canali 2k e 2k+1) | 2 VBPW34S con filtro di bias 1k + 100 nF C0G. OPA4140: A/B preamplificatori di carica, C/D shaper CR-RC invertente ×50 (τ = 1 µs). TLV3502 doppio comparatore con soglia VTH (trim per canale DNP). 74LVC74A doppio latch (azzerato da CS_Y3). OPA2365 doppio rilevatore di picco con BAS416 e hold 1 nF C0G, reset con BSS138. Iniezione di carica di test da 0,5 pF. |
| Acquisizione | MCP23S17 *mappa dei colpi* (Y5): 16 latch in una transazione. MCP23S17 *di controllo* (Y7, interrupt manager): indirizzo del mux, FAULT, HIT_ANY, abilitazione del test. 2× TMUX1108 (16:1) → buffer OPA2365 → 47 Ω + 1 nF → ADS8326 (Y0). HIT_ANY = OR dei 16 latch (2× 74HC30 + 74LVC1G32). |
| Bias | DAC61402: OUTA = bias comune (shunt 10k con INA239, 125 pA/LSB), OUTB = soglia VTH (0–1,56 V, ~0,4 mV/LSB). TMP117 al centro della matrice. |
| bus-pnp | J_IN/J_OUT XUNPU FPC-05F-28PH20, 74HC283/85/138, buffer LVC, ESD, EEPROM 25AA02E48, HIT# (74LVC1G123 + 74LVC1G06). |

## Mappa degli indirizzi del piano (74HC138)

| Y | Funzione |
|---|---|
| 0 | ADS8326 (ampiezza del canale selezionato dal mux) |
| 1 | DAC61402 (bias e soglia) |
| 2 | INA239 (corrente di buio totale) |
| 3 | Strobe: azzera i 16 latch e i 16 picchi |
| 4 | Strobe: gradino di test (se TEST_EN_N = 0), ~3,3 mV su 0,5 pF ≈ 1,6 fC per canale |
| 5 | MCP23S17 mappa dei colpi |
| 6 | EEPROM 25AA02E48 (identità del piano) |
| 7 | MCP23S17 di controllo (interrupt manager, ALERT#) |

## Sequenza di un evento

1. Uno o più comparatori scattano: i latch memorizzano i canali e i picchi tengono l'ampiezza.
2. HIT_ANY sale e genera un impulso di ~170–200 ns su HIT#. È un solo fronte per evento: gli impulsi dei piani colpiti dalla stessa particella si sovrappongono.
3. Il master marca il tempo del fronte e legge da ogni piano la mappa dei colpi (Y5).
4. Per ogni canale colpito il master imposta il mux (Y7) e converte il picco (Y0).
5. Infine azzera latch e picchi con un accesso a Y3.

## Scelte

- **OPA4140 al posto dell'OPA4172.** Ingresso JFET: rumore di corrente trascurabile e 10 pA massimi di corrente di polarizzazione. Rumore di tensione 5,1 nV/√Hz contro 7, quindi ENC serie circa −25 %. 11 MHz di banda, uscita rail-to-rail. Il quad copre preamplificatore e shaper di due canali.
- **Shaper a uno stadio ×50.** Si risparmia un operazionale per canale. Con 11 MHz la banda a guadagno 50 è ~200 kHz, compatibile con τ = 1 µs.
- **Peak hold con l'ingresso invertente sul condensatore.** L'OPA2365 ha 0,2 pA di corrente di polarizzazione, quindi niente buffer per canale: un solo buffer dopo il mux protegge l'hold dal kickback dell'ADC.
- **Mux TMUX1108 (3 pA).** Le perdite sul condensatore da 1 nF sono trascurabili nei tempi di lettura. L'ADG706 è un'alternativa equivalente: il suo datasheet non era raggiungibile, quindi ho scelto il TMUX1108 di cui ho verificato il pinout.

## Stato (2026-10-14)

- Schema: **ERC 0**, 486 componenti.
- PCB: **140 × 120 mm, 4 strati** (segnali, GND, alimentazioni, segnali). Sensori sul lato inferiore, al centro, in griglia 4×4. Elettronica di canale a gruppi sul lato superiore, logica comune in basso. J_IN a sinistra e J_OUT a destra, fori M3 agli angoli nelle stesse posizioni su ogni piano, così i piani si impilano. **Non sbrogliato.**
- 4 strati dovrebbero bastare; 6 strati (due piani di massa ai lati dei segnali analogici) sono da valutare se lo sbroglio dei 16 canali risulta troppo denso.
- DRC: centinaia di serigrafie sovrapposte e non connessi (KiCad si ferma a 199/499 per categoria), più 59 clearance tra componenti vicini o dentro i footprint a passo fine. Tutto atteso prima dello sbroglio.

## Stima dei costi dei componenti per piano

Prezzi indicativi per 10 piani (distributori, ottobre 2026), esclusi PCB e montaggio: **circa 140–170 USD per piano**.

| Voce | Quantità | Stima |
|---|---|---|
| OPA4140 | 8 | 35–45 |
| TLV3502 | 8 | 18–24 |
| OPA2365 | 9 | 15–20 |
| VBPW34S | 16 | 10–15 |
| DAC61402, INA239, ADS8326, TMP117 | 1 ciascuno | 20–25 |
| MCP23S17 ×2, TMUX1108 ×2, logica 74HC/LVC, EEPROM | — | 10–12 |
| Condensatori C0G 100 nF 100 V 1206 | 17 | 5–8 |
| Altri passivi (~350), Rf ad alto valore, connettori FPC, ESD | — | 15–20 |

## Punti aperti

- Valori di `${RF}`, `${CF}` e `${VBIAS}` dai dati del PianoTest.
- Il gradino di test dipende dalla tensione a 3,3 V del bus: per la calibrazione assoluta misurare il 3V3, oppure sostituire il partitore con un riferimento.
- La capacità di iniezione da 0,5 pF aggiunge 0,5 pF all'ingresso di ogni canale: si può lasciare DNP dopo la calibrazione.
- Quote del footprint FPC da confrontare con il disegno XUNPU.

Footprint `MIKILAB_*` dalla libreria esterna MIKILAB (variabile `${MIKILAB}`), non inclusa nel repository.

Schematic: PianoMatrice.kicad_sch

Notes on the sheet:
PianoMatrice - piano MuonScope 4x4 VBPW34S (passo 10 mm) sul bus MIKILAB REV5.1. Variabili: RF=${RF}, CF=${CF}, VBIAS=${VBIAS}. Vedi README.md.

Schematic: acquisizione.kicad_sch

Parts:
C1001: 1nF C0G; C_0603_1608Metric
C1002: 100nF; C_0603_1608Metric
C1003, C1004, C1005, C1006, C1007, C1008, C1009, C1010, C1011: 100nF; C_0402_1005Metric
R1001: 47R; R_0603_1608Metric
R1002, R1006: 100k; R_0603_1608Metric
R1003: 100R; R_0603_1608Metric
R1004, R1005: 10k; R_0603_1608Metric
TP1001: HIT_ANY; TestPoint_Pad_D1.0mm
TP1002: MUX_D; TestPoint_Pad_D1.0mm
TP1003: TEST_INJ; TestPoint_Pad_D1.0mm
U1001, U1002: MCP23S17-E/ML; QFN-28-1EP_6x6mm_P0.65mm_EP4.25x4.25mm; MPN MCP23S17-E/ML
U1003, U1004: TMUX1108PWR; TSSOP-16_4.4x5mm_P0.65mm; MPN TMUX1108PWR
U1005: OPA2365AIDR; SOIC-8_3.9x4.9mm_P1.27mm; MPN OPA2365AIDR
U1006: ADS8326IDGKT; SOP65P490X110-8N; MPN ADS8326IDGKT
U1007, U1008: 74HC30PW; TSSOP-14_4.4x5mm_P0.65mm; MPN 74HC30PW
U1009: SN74LVC1G32DBVR; SOT-23-5; MPN SN74LVC1G32DBVR
U1010: SN74LVC1G04DBVR; SOT-23-5; MPN SN74LVC1G04DBVR
U1011: SN74LVC1G02DBVR; SOT-23-5; MPN SN74LVC1G02DBVR

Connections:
2V5_REF: U1006.1 (REF); also elsewhere on the board
+3V3: C1003.1, C1004.1, C1005.1, C1006.1, C1007.1, C1008.1, C1009.1, C1010.1, C1011.1, R1004.1, R1005.1, U1001.5 (VDD), U1001.11 (A0), U1002.5 (VDD), U1003.13 (VDD), U1004.13 (VDD), U1005.8 (V+), U1006.8 (VDD), U1007.14 (VCC), U1008.14 (VCC), U1009.5 (VCC), U1010.5 (VCC), U1011.5 (VCC); also elsewhere on the board
/Acquisizione/ADC_BUF: R1001.1, U1005.1 (OUTA), U1005.2 (-INA)
/Acquisizione/ADC_IN: C1001.1, R1001.2, U1006.2 (+IN)
/Acquisizione/HIT_HI: U1008.8 (Y), U1009.2 (B)
/Acquisizione/HIT_LO: U1007.8 (Y), U1009.1 (A)
/Acquisizione/MCP_RST: C1002.1, R1004.2, U1001.14 (~RESET), U1002.14 (~RESET)
/Acquisizione/MUX_A0: U1002.17 (GPA0), U1003.1 (A0), U1004.1 (A0)
/Acquisizione/MUX_A1: U1002.18 (GPA1), U1003.16 (A1), U1004.16 (A1)
/Acquisizione/MUX_A2: U1002.19 (GPA2), U1003.15 (A2), U1004.15 (A2)
/Acquisizione/MUX_D: TP1002.1, U1003.8 (D), U1004.8 (D), U1005.3 (+INA)
/Acquisizione/MUX_EN_HI: U1002.21 (GPA4), U1004.2 (EN)
/Acquisizione/MUX_EN_LO: U1002.20 (GPA3), U1003.2 (EN)
/Acquisizione/OPB_UNUSED: U1005.6 (-INB), U1005.7 (OUTB)
/Acquisizione/TEST_EN_N: R1005.2, U1002.24 (GPA7), U1011.2 (B)
/Acquisizione/TEST_STEP: R1002.1, U1011.4 (Y)
CS_ADC: U1006.5 (~CS); also elsewhere on the board
CS_HITMAP: U1001.7 (~CS); also elsewhere on the board
CS_MCP: U1002.7 (~CS); also elsewhere on the board
CS_Y3: U1010.2 (A); also elsewhere on the board
CS_Y4: U1011.1 (A); also elsewhere on the board
GND: C1001.2, C1002.2, C1003.2, C1004.2, C1005.2, C1006.2, C1007.2, C1008.2, C1009.2, C1010.2, C1011.2, R1003.2, R1006.2, U1001.6 (VSS), U1001.12 (A1), U1001.13 (A2), U1001.29 (EP), U1002.6 (VSS), U1002.11 (A0), U1002.12 (A1), U1002.13 (A2), U1002.29 (EP), U1003.3 (VSS), U1003.14 (GND), U1004.3 (VSS), U1004.14 (GND), U1005.4 (V-), U1005.5 (+INB), U1006.3 (-IN), U1006.4 (GND), U1007.7 (GND), U1008.7 (GND), U1009.3 (GND), U1010.3 (GND), U1011.3 (GND); also elsewhere on the board
HIT_ANY: TP1001.1, U1002.23 (GPA6), U1009.4 (Y); also elsewhere on the board
HOLD0: U1003.4 (S1); also elsewhere on the board
HOLD1: U1003.5 (S2); also elsewhere on the board
HOLD2: U1003.6 (S3); also elsewhere on the board
HOLD3: U1003.7 (S4); also elsewhere on the board
HOLD4: U1003.12 (S5); also elsewhere on the board
HOLD5: U1003.11 (S6); also elsewhere on the board
HOLD6: U1003.10 (S7); also elsewhere on the board
HOLD7: U1003.9 (S8); also elsewhere on the board
HOLD8: U1004.4 (S1); also elsewhere on the board
HOLD9: U1004.5 (S2); also elsewhere on the board
HOLD10: U1004.6 (S3); also elsewhere on the board
HOLD11: U1004.7 (S4); also elsewhere on the board
HOLD12: U1004.12 (S5); also elsewhere on the board
HOLD13: U1004.11 (S6); also elsewhere on the board
HOLD14: U1004.10 (S7); also elsewhere on the board
HOLD15: U1004.9 (S8); also elsewhere on the board
MCP_INTA: U1002.16 (INTA); also elsewhere on the board
MISO_L: U1001.10 (SO), U1002.10 (SO), U1006.6 (DOUT); also elsewhere on the board
MOSI_L: U1001.9 (SI), U1002.9 (SI); also elsewhere on the board
PK_RST: R1006.1, U1010.4 (Y); also elsewhere on the board
PL_FAULT: U1002.22 (GPA5); also elsewhere on the board
Q0: U1001.17 (GPA0); also elsewhere on the board
Q1: U1001.18 (GPA1); also elsewhere on the board
Q2: U1001.19 (GPA2); also elsewhere on the board
Q3: U1001.20 (GPA3); also elsewhere on the board
Q4: U1001.21 (GPA4); also elsewhere on the board
Q5: U1001.22 (GPA5); also elsewhere on the board
Q6: U1001.23 (GPA6); also elsewhere on the board
Q7: U1001.24 (GPA7); also elsewhere on the board
Q8: U1001.25 (GPB0); also elsewhere on the board
Q9: U1001.26 (GPB1); also elsewhere on the board
Q10: U1001.27 (GPB2); also elsewhere on the board
Q11: U1001.28 (GPB3); also elsewhere on the board
Q12: U1001.1 (GPB4); also elsewhere on the board
Q13: U1001.2 (GPB5); also elsewhere on the board
Q14: U1001.3 (GPB6); also elsewhere on the board
Q15: U1001.4 (GPB7); also elsewhere on the board
QN0: U1007.1 (I0); also elsewhere on the board
QN1: U1007.2 (I1); also elsewhere on the board
QN2: U1007.3 (I2); also elsewhere on the board
QN3: U1007.4 (I3); also elsewhere on the board
QN4: U1007.5 (I4); also elsewhere on the board
QN5: U1007.6 (I5); also elsewhere on the board
QN6: U1007.11 (I6); also elsewhere on the board
QN7: U1007.12 (I7); also elsewhere on the board
QN8: U1008.1 (I0); also elsewhere on the board
QN9: U1008.2 (I1); also elsewhere on the board
QN10: U1008.3 (I2); also elsewhere on the board
QN11: U1008.4 (I3); also elsewhere on the board
QN12: U1008.5 (I4); also elsewhere on the board
QN13: U1008.6 (I5); also elsewhere on the board
QN14: U1008.11 (I6); also elsewhere on the board
QN15: U1008.12 (I7); also elsewhere on the board
SCLK_L: U1001.8 (SCK), U1002.8 (SCK), U1006.7 (DCLOCK); also elsewhere on the board
TEST_INJ: R1002.2, R1003.1, TP1003.1; also elsewhere on the board

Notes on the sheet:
MAPPA DEI COLPI: MCP23S17 U1001 (indirizzo Y5, CS_HITMAP) legge i 16 latch Q0-Q15 in una transazione. CONTROLLO: MCP23S17 U1002 (Y7, interrupt manager) - mux, test, FAULT, HIT_ANY.
AMPIEZZA: 2x TMUX1108 (8:1, 3 pA) sui 16 HOLD -> buffer OPA2365 -> 47R + 1 nF -> ADS8326 (Y0). Reset di latch e picchi: accesso all'indirizzo 3 (CS_Y3). Gradino di test: accesso all'indirizzo 4 con TEST_EN_N basso.
HIT_ANY = OR dei 16 latch (2x 74HC30 sui ~Q + 74LVC1G32): un solo fronte per evento fino al reset.

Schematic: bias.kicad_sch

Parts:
C1101, C1102: 1uF/100V; C_1206_3216Metric
C1103: 100nF/100V; C_1206_3216Metric
C1104, C1105: 470pF/100V; C_1206_3216Metric; not fitted
C1106: 100nF/100V C0G; C_1206_3216Metric; MPN C3216C0G2A104J160AE
C1107, C1108, C1109, C1110, C1111, C1112: 100nF; C_0603_1608Metric
D1101: BAT54S; SOT-23; MPN BAT54S
R1101: 100R; R_0805_2012Metric
R1102: 10k 0.1%; R_0805_2012Metric; MPN ERA-6ARB103V
R1103: 22k; R_0603_1608Metric
R1104, R1105: 10k; R_0603_1608Metric
TP1101: VBIAS_SH; TestPoint_Pad_D1.0mm
TP1102: VTH; TestPoint_Pad_D1.0mm
U1101: DAC61402RHBR; VQFN32_RHB_TEX; MPN DAC61402RHBR
U1102: INA239AIDGSR; VSSOP_9AIDGST_TEX; MPN INA239AIDGSR
U1103: TMP117AIDRVR; WSON-6-1EP_2x2mm_P0.65mm_EP1x1.6mm; MPN TMP117AIDRVR

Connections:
+3V3: C1109.1, C1111.1, C1112.1, D1101.2 (K2), R1105.1, U1101.15 (IOVDD), U1101.16 (~CLR), U1101.32 (~RST), U1102.6 (VS), U1103.5 (V+); also elsewhere on the board
+5V: C1108.1, U1101.30 (DVDD); also elsewhere on the board
/Bias/AVDD_DAC: C1101.1, C1102.1, C1103.1, R1101.2, U1101.28 (AVDD)
/Bias/CCOMPA: C1104.1, U1101.7 (CCOMPA)
/Bias/CCOMPB: C1105.1, U1101.18 (CCOMPB)
/Bias/DAC_OUTA: C1104.2, R1102.1, U1101.6 (SENSEPA), U1101.8 (OUTA), U1102.10 (IN+)
/Bias/DAC_OUTB: C1105.2, R1103.1, U1101.17 (OUTB), U1101.19 (SENSEPB)
/Bias/DAC_REF: C1110.1, U1101.26 (REFIO)
CS_DAC: U1101.12 (~SYNC); also elsewhere on the board
CS_INA: U1102.1 (CS); also elsewhere on the board
GND: C1101.2, C1102.2, C1103.2, C1106.2, C1107.2, C1108.2, C1109.2, C1110.2, C1111.2, C1112.2, D1101.1 (A1), R1104.2, U1101.5 (SENSENA), U1101.13 (~LDAC), U1101.14 (GND), U1101.20 (SENSENB), U1101.25 (REFGND), U1101.27 (AVSS), U1101.29 (AGND), U1101.33 (EP), U1102.7 (GND), U1103.2 (GND), U1103.4 (ADD0), U1103.7 (EP); also elsewhere on the board
I2C_SCL: U1103.1 (SCL); also elsewhere on the board
I2C_SDA: U1103.6 (SDA); also elsewhere on the board
MISO_L: U1101.9 (SDO), U1102.4 (MISO); also elsewhere on the board
MOSI_L: U1101.11 (SDIN), U1102.2 (MOSI); also elsewhere on the board
PL_FAULT: R1105.2, U1101.31 (~FAULT), U1102.3 (ALERT), U1103.3 (ALERT); also elsewhere on the board
SCLK_L: U1101.10 (SCLK), U1102.5 (SCLK); also elsewhere on the board
VBIAS_SH: C1106.1, R1102.2, TP1101.1, U1102.8 (VBUS), U1102.9 (IN-); also elsewhere on the board
VHV_36V: R1101.1; also elsewhere on the board
VTH: C1107.1, D1101.3 (K1/A2), R1103.2, R1104.1, TP1102.1; also elsewhere on the board

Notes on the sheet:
BIAS: DAC61402 OUTA (V_BIAS nominale ${VBIAS}) -> shunt 10k (INA239, 125 pA/LSB) -> VBIAS_SH -> 16 filtri RC per diodo (1k + 100 nF C0G nei fogli dei canali).
SOGLIA: OUTB in range 0-5 V -> partitore 22k/10k -> VTH (0-1.56 V, ~0.4 mV/LSB), unica per il piano. TMP117 da piazzare al centro della matrice (lato sensori).
